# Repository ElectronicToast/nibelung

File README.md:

Teensy 4.0-based RGB LED controller

## Description
Nibelung is a breakout board for the Teensy 4.0 intended for controlling WS2811-based addressable RGB LED strips using the [OctoWS2811 library](https://www.pjrc.com/teensy/td_libs_OctoWS2811.html). Eight LED outputs on Teensy pins 2 to 9 are provided through screw terminals. An audio jack enables music reactive effects with stereo audio through the Teensy's internal ADCs. User pushbuttons and LEDs are provided.

The board is named after the Nibelungen dwarves from Richard Wagner's Ring Cycle.

&nbsp;

&nbsp;

## Usage
Power the board with either USB power through the Teensy or one external power input: 6-12 V (recommended) through `VIN` or regulated 5V through `5V`.

While not designed for Teensy 4.1, the board may be compatible. 

## Licensing
This project is released under the terms of the MIT License.

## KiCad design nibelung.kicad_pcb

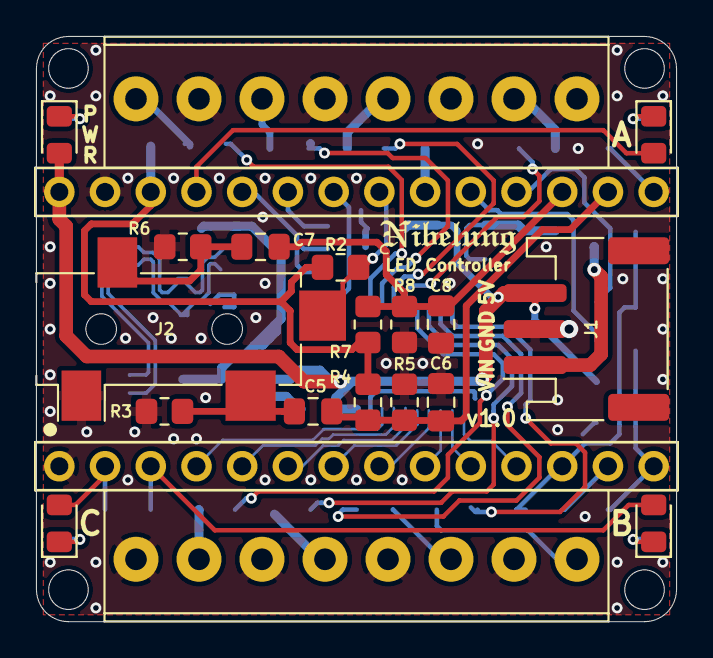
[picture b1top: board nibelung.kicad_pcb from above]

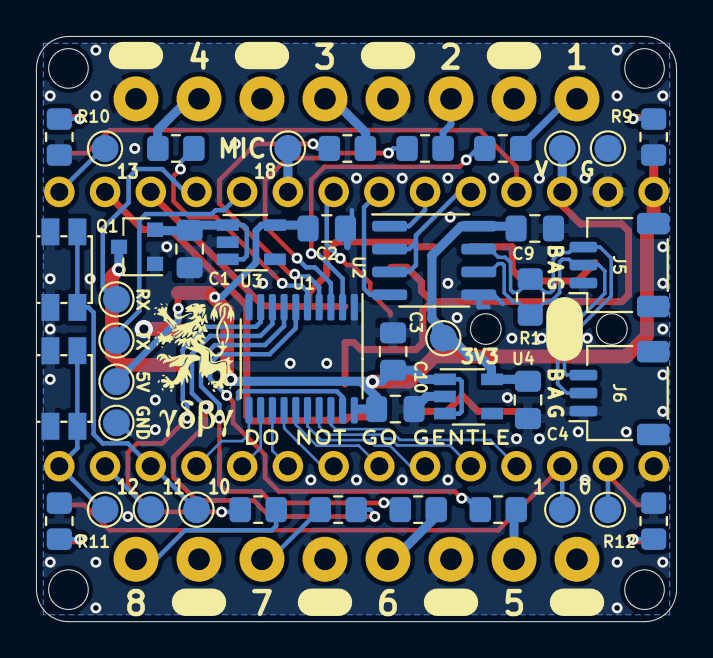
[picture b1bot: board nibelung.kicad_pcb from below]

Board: 2 copper layers, 35.6 x 32.5 mm, 66 parts (42 on the bottom side), 54 nets.

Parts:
A1: Teensy4.0; Teensy40_Socket
C1, C2, C5, C7: 10uF; C_0805_2012Metric_Pad1.18x1.45mm_HandSolder
C3, C4: 1uF; C_0805_2012Metric_Pad1.18x1.45mm_HandSolder
C6, C8: 47nF; C_0805_2012Metric_Pad1.18x1.45mm_HandSolder
C9, C10: 0.1uF; C_0805_2012Metric_Pad1.18x1.45mm_HandSolder
D1: RED; LED_0805_2012Metric_Pad1.15x1.40mm_HandSolder
D2: GRN; LED_0805_2012Metric_Pad1.15x1.40mm_HandSolder
D3: YEL; LED_0805_2012Metric_Pad1.15x1.40mm_HandSolder
D4: BLU; LED_0805_2012Metric_Pad1.15x1.40mm_HandSolder
H1, H2, H3, H4: M2; MountingHole_2.2mm_M2
J1: JST_PH_01x03; JST_PH_S3B-PH-SM4-TB_1x03-1MP_P2.00mm_Horizontal
J2: AudioJack3-TSW; Jack_CUI_SJ-3524
J3, J4: ScrewTerm_01x08_2.54mm; TerminalBlock_Molex_393570008_1x08_P3.50mm_Horizontal
J5, J6: JST_SH_01x03; JST_SH_SM03B-SRSS-TB_1x03-1MP_P1.00mm_Horizontal
Q1: DMP3099L; SOT-23
R1: 120; R_0805_2012Metric_Pad1.20x1.40mm_HandSolder
R2: 1M; R_0805_2012Metric_Pad1.20x1.40mm_HandSolder
R3, R4, R5, R6, R7, R8: 100k; R_0805_2012Metric_Pad1.20x1.40mm_HandSolder
R9: 1k; R_0805_2012Metric_Pad1.20x1.40mm_HandSolder
R10: 330; R_0805_2012Metric_Pad1.20x1.40mm_HandSolder
R11: 470; R_0805_2012Metric_Pad1.20x1.40mm_HandSolder
R12, R13, R14, R15, R16, R17, R18, R19, R20: 100; R_0805_2012Metric_Pad1.20x1.40mm_HandSolder
SW1, SW2: PTS840 GK; SW_Push_1P1T_NO_CK_PTS840
TP1, TP2, TP3, TP4, TP5, TP6, TP7, TP8, TP9, TP10, TP11, TP12, TP13, TP14: Pad; TestPoint_Pad_D1.5mm
U1: 74HCT245; TSSOP-20_4.4x6.5mm_P0.65mm
U2: LTC2850xS8; SOIC-8_3.9x4.9mm_P1.27mm
U3: MIC5219-5.0YM5; TSOT-23-5
U4: MIC5317-3.3YM5; TSOT-23-5

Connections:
+3V3: C4.1, C9.2, TP14.1, U2.8, U4.5
+3V3A: A1.26, R2.1, R4.1, R7.1, TP1.1
+5V: A1.28, C2.1, C3.1, C10.2, D1.2, J1.3, TP4.1, U1.20, U3.5, U4.1, U4.3
/AUD_DET: A1.21, J2.TN, R2.2
/AUD_L: C5.2, J2.T, R3.1
/AUD_L_ADC: A1.16, C5.1, C6.1, R4.2, R5.1
/AUD_R: C7.2, J2.R, R6.1
/AUD_R_ADC: A1.17, C7.1, C8.1, R7.2, R8.1
/BTNA: A1.12, SW1.2, TP8.1
/BTNB: A1.14, SW2.2, TP10.1
/D+: J5.2, J6.2, R1.1, U2.6
/D-: J5.3, J6.3, R1.2, U2.7
/DATA_RX: A1.23, U2.1
/DATA_TX: A1.22, U2.4
/DATA_TXEN: A1.24, U2.2, U2.3
/INDA: A1.25, D2.2
/INDB: A1.3, D3.2, TP13.1
/INDC: A1.2, D4.2, TP12.1
/LED1: A1.4, U1.18
/LED2: A1.5, U1.17
/LED3: A1.6, U1.16
/LED4: A1.7, U1.15
/LED5: A1.8, U1.14
/LED6: A1.9, U1.13
/LED7: A1.10, U1.12
/LED8: A1.11, U1.11
/LED_OUT1: J3.8, R13.1
/LED_OUT2: J3.6, R14.1
/LED_OUT3: J3.4, R15.1
/LED_OUT4: J3.2, R16.1
/LED_OUT5: J4.2, R17.1
/LED_OUT6: J4.4, R18.1
/LED_OUT7: J4.6, R19.1
/LED_OUT8: J4.8, R20.1
/MIC_IN: A1.20, TP3.1
/UART_RX: A1.18, TP7.1
/UART_TX: A1.19, TP6.1
GND: A1.1, A1.27, C1.2, C2.2, C3.2, C4.2, C6.2, C8.2, C9.1, C10.1, J1.2, J2.S, J3.1, J3.3, J3.5, J3.7, J4.1, J4.3, J4.5, J4.7, J5.1, J6.1, Q1.1, R3.2, R5.2, R6.2, R8.2, R9.2, R10.2, R11.2, R12.2, SW1.1, SW2.1, TP2.1, TP5.1, U1.1, U1.10, U1.19, U2.5, U3.2, U4.2
unnamed: A1.13, TP9.1
unnamed: A1.15, TP11.1
unnamed: C1.1, Q1.2, U3.1, U3.3
unnamed: D1.1, R9.1
unnamed: D2.1, R10.1
unnamed: D3.1, R11.1
unnamed: D4.1, R12.1
unnamed: R13.2, U1.2
unnamed: R14.2, U1.3
unnamed: R15.2, U1.4
unnamed: R16.2, U1.5
unnamed: R17.2, U1.6
unnamed: R18.2, U1.7
unnamed: R19.2, U1.8
unnamed: R20.2, U1.9
VIN: J1.1, Q1.3

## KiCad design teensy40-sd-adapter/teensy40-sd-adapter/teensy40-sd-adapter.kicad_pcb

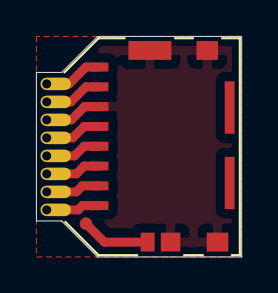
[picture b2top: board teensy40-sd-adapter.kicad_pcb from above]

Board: 2 copper layers, 11.4 x 12.2 mm, 3 parts (0 on the bottom side), 9 nets.

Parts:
J1: Micro_SD_Card_Det_Single; microSD_Molex_1051620001
J2: Conn_01x08; Teensy40_SD_Castellated
TP1: TestPoint; Pad_0.7mm

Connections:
/CLK: J1.5, J2.4
/CMD: J1.3, J2.6
/DAT0: J1.7, J2.2
/DAT1: J1.8, J2.1
/DAT2: J1.1, J2.8
/DAT3: J1.2, J2.7
/VDD: J1.4, J2.5
/VSS: J1.6, J1.10, J2.3
unnamed: J1.9, TP1.1

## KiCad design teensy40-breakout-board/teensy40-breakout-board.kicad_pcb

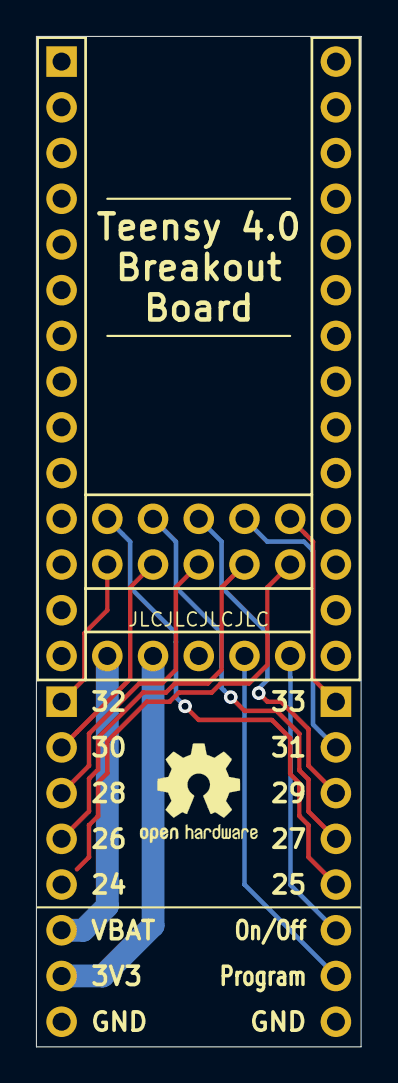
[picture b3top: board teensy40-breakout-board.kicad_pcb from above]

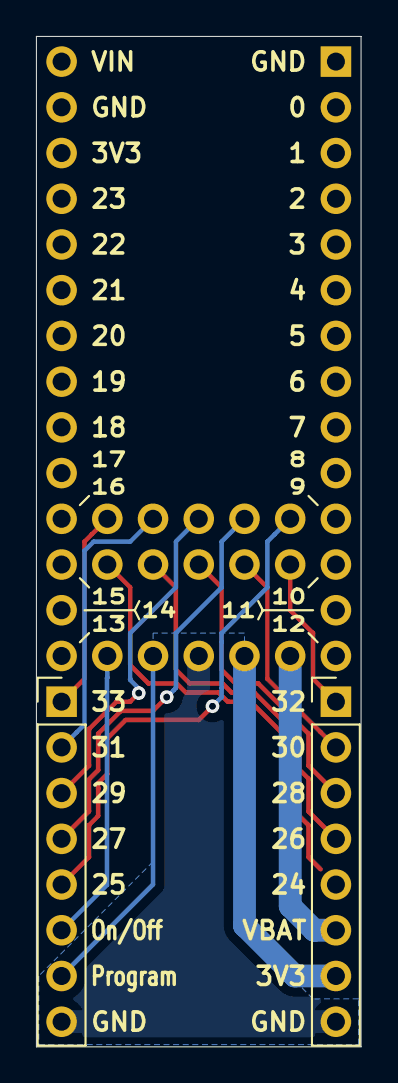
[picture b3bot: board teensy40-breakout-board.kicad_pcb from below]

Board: 2 copper layers, 18.0 x 56.1 mm, 3 parts (2 on the bottom side), 15 nets.

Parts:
J1, J2: Conn_01x08; PinHeader_1x08_P2.54mm_Vertical
U1: Teensy4.0_WithBottomAndEdge; Teensy40_Socket_WithBottomAndEdge

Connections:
+3V3: J1.7, U1.42
GND: J1.8, J2.8, U1.41
unnamed: J1.1, U1.33
unnamed: J1.2, U1.32
unnamed: J1.3, U1.31
unnamed: J1.4, U1.30
unnamed: J1.5, U1.29
unnamed: J2.1, U1.38
unnamed: J2.2, U1.37
unnamed: J2.3, U1.36
unnamed: J2.4, U1.35
unnamed: J2.5, U1.34
unnamed: J2.6, U1.39
unnamed: J2.7, U1.40
VCC: J1.6, U1.43

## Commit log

2019-03-31 Add project
2019-07-14 Update license
2019-07-14 Continue design
2019-07-15 Make symbols and footprints
2019-08-30 Fixed WS2811 chip name
2019-11-08 Add Teensy 4.0 symbol
2019-11-08 Add Teensy 4.0 footprint
2019-11-08 Add schematic backup files to gitignore
2019-11-08 Begin updating schematic to Teensy 4.0
2019-11-08 Remove Teensy 3.x artifacts and add pullup to FSYNC
2019-12-23 Make additional Teensy 4.0 symbols that break out more of the pins
2019-12-24 Make Teensy 4.0 socket footprints
2019-12-24 Update Teensy 4.0 symbols with corresponding default footprints
2019-12-24 Begin making breakout board for Teensy 4.0
2019-12-25 Complete routing
2019-12-25 Add top silkscreen labels
2019-12-25 Label all breakout pins
2019-12-26 Make castellated hole footprint for microSD card adapter board
2019-12-26 Make microSD adapter board; need to select card socket
2019-12-26 Add microSD socket symbol
2019-12-26 Fix footprint
2019-12-27 Make pad 9 centered for easy routing
2019-12-27 Remove second line of holes
2019-12-27 Break out detect pin for possible prototyping use
2019-12-27 Fix mislabeled ground pin
2019-12-27 Make adapter PCB
2019-12-30 Move files and redesign for fab with castellated holes
2019-12-30 Generate Gerbers
2019-12-30 Make adapter with a Arduino HC-05 programming adapter board for panel production
2019-12-31 Revise routing
2019-12-31 Clean up positions
2019-12-31 Clean up more
2019-12-31 Add more silkscreen labels
2019-12-31 Prepare for paneling
2019-12-31 Make panel
2019-12-31 Finish panel
2019-12-31 Put edge and Vccut on same Gerber file
2019-12-31 Add separate panels
2019-12-31 Move edge rail to make less than 100mm long
2019-12-31 Rename edge and Vcut file
2020-12-25 Move breakout board projects
2020-12-25 Create LICENSE
2020-12-25 Begin redesign
2020-12-25 Update logos
2020-12-26 Edit sheet layout
2020-12-26 Add terminal block footprints
2020-12-27 Add 8 pin terminal block and update descriptions
2021-01-02 Add SJ-3524 audio jack symbol
2021-01-02 Add most connectors and RS-485 transceiver
2021-01-02 Modify audio circuit to typical cap coupling topology
2021-01-02 Set up design rules
2021-01-02 Begin preliminary placement
2021-01-03 Add power connectors
2021-01-03 Add 2.54mm screw terminal
2021-01-03 Adjust for M2.5 mounting holes
2021-01-04 Add indicator LEDs
2021-01-04 Swap power and RS-485 connector locations
2021-01-04 Revise placement and label output connections
2021-01-04 Replace 2-pin PH power connector with 3-pin PH
2021-01-09 Add linear regulators
2021-01-09 Add right angle pushbuttons
2021-01-15 Continue placement
2021-01-16 Length-match differential pair traces
2021-01-16 Replace 2.54mm pitch terminals with 3.5mm pitch ones
2021-01-17 Make board less wide
2021-01-18 Add properly colored STEP models
2021-03-28 Finish layout
2021-03-28 Clean up via holes to minimize interrupting silkscreen
2021-03-28 Add renders
